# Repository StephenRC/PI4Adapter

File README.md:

# PI4Adapter
PI3 or PI4 to Duet 3

Duet 3 Mini 5+ mount directly on it with the board hanging off the side,  5vdc required.

Deut 3 6HC, mount of the board, needs a extension to the 26 pin socket to get the board high enough.  PI4 requires external 5vdc.

The JST-XH is for addons, like the official PI Touchscreen

Round Trakcs plugin used.  Add it in with the KiCAD plugin mamnager.

USB C connector: Didn't fit, adjusted it.  Need to test again

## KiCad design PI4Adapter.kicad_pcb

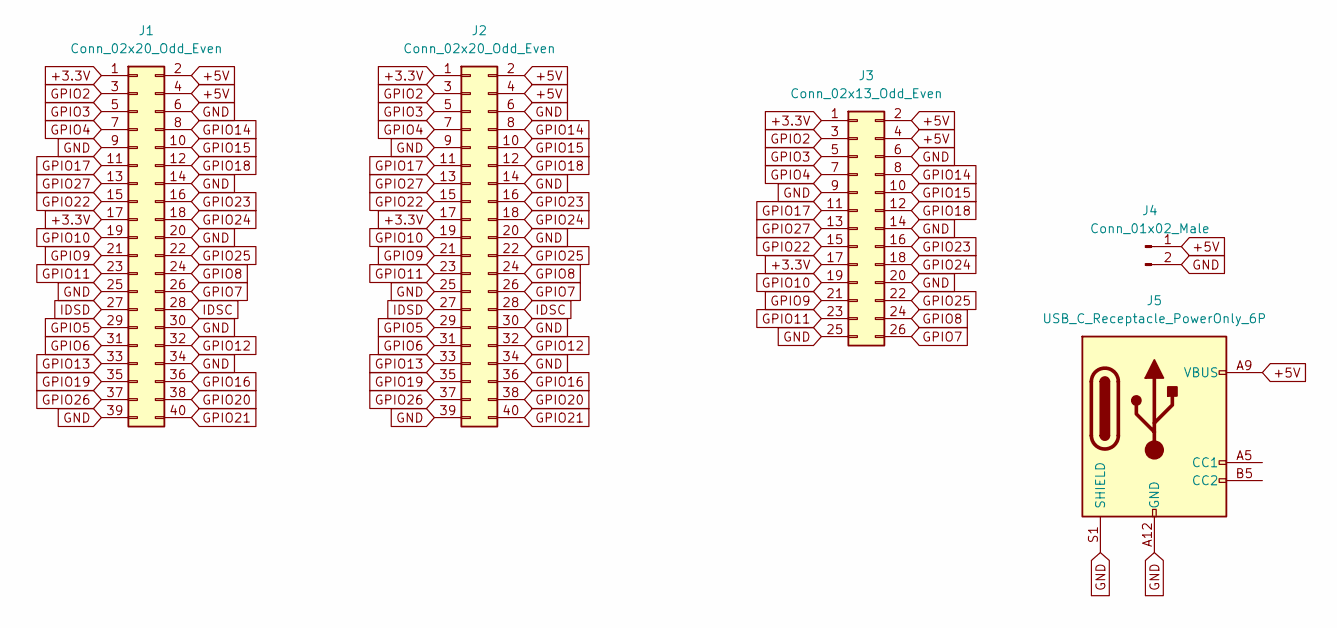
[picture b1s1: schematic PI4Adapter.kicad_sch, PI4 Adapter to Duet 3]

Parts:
J1: Conn_02x20_Odd_Even; PinSocket_2x20_P2.54mm_Vertical
J2: Conn_02x20_Odd_Even; PinHeader_2x20_P2.54mm_Vertical
J3: Conn_02x13_Odd_Even; PinSocket_2x13_P2.54mm_Vertical
J4: Conn_01x02_Male; JST_XH_S2B-XH-A_1x02_P2.50mm_Horizontal
J5: USB_C_Receptacle_PowerOnly_6P; USB_C_Receptacle_GCT_USB4135-GF-A_6P_TopMnt_Horizontal

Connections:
+3.3V: J1.1, J1.17, J2.1, J2.17, J3.1, J3.17
+5V: J1.2, J1.4, J2.2, J2.4, J3.2, J3.4, J4.1, J5.A9 (VBUS), J5.B9 (VBUS)
GND: J1.6, J1.9, J1.14, J1.20, J1.25, J1.30, J1.34, J1.39, J2.6, J2.9, J2.14, J2.20, J2.25, J2.30, J2.34, J2.39, J3.6, J3.9, J3.14, J3.20, J3.25, J4.2, J5.A12 (GND), J5.B12 (GND), J5.S1 (SHIELD)
GPIO2: J1.3, J2.3, J3.3
GPIO3: J1.5, J2.5, J3.5
GPIO4: J1.7, J2.7, J3.7
GPIO5: J1.29, J2.29
GPIO6: J1.31, J2.31
GPIO7: J1.26, J2.26, J3.26
GPIO8: J1.24, J2.24, J3.24
GPIO9: J1.21, J2.21, J3.21
GPIO10: J1.19, J2.19, J3.19
GPIO11: J1.23, J2.23, J3.23
GPIO12: J1.32, J2.32
GPIO13: J1.33, J2.33
GPIO14: J1.8, J2.8, J3.8
GPIO15: J1.10, J2.10, J3.10
GPIO16: J1.36, J2.36
GPIO17: J1.11, J2.11, J3.11
GPIO18: J1.12, J2.12, J3.12
GPIO19: J1.35, J2.35
GPIO20: J1.38, J2.38
GPIO21: J1.40, J2.40
GPIO22: J1.15, J2.15, J3.15
GPIO23: J1.16, J2.16, J3.16
GPIO24: J1.18, J2.18, J3.18
GPIO25: J1.22, J2.22, J3.22
GPIO26: J1.37, J2.37
GPIO27: J1.13, J2.13, J3.13
IDSC: J1.28, J2.28
IDSD: J1.27, J2.27

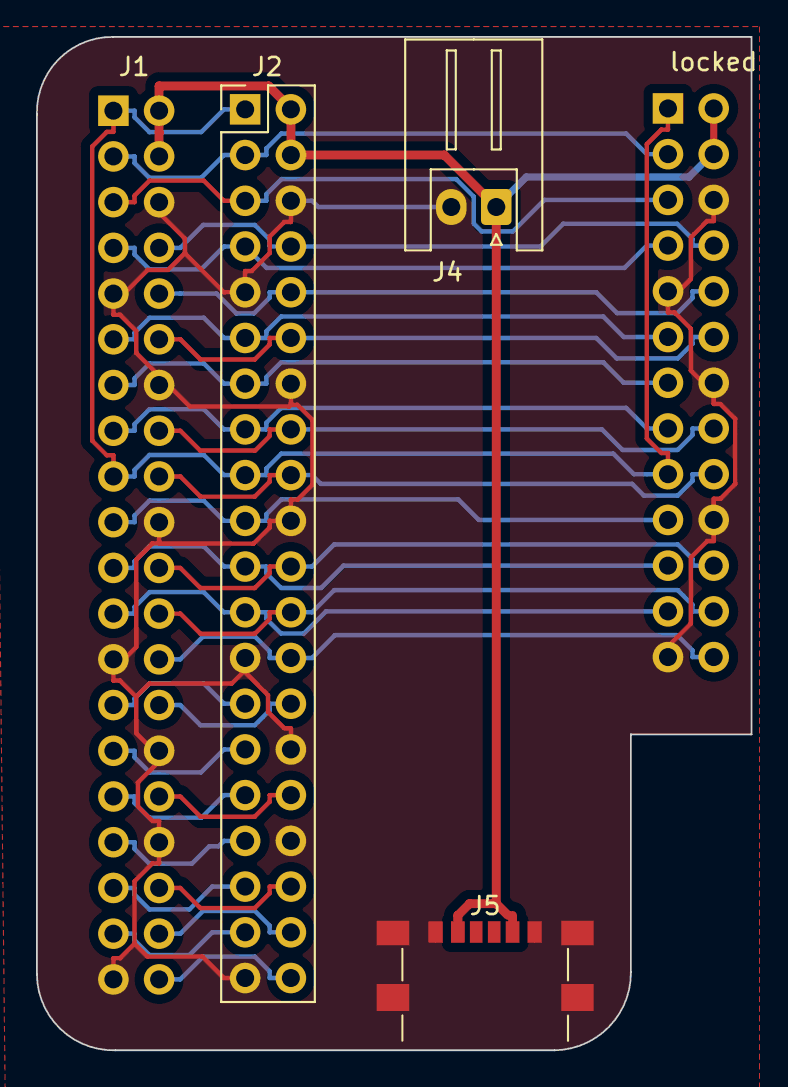
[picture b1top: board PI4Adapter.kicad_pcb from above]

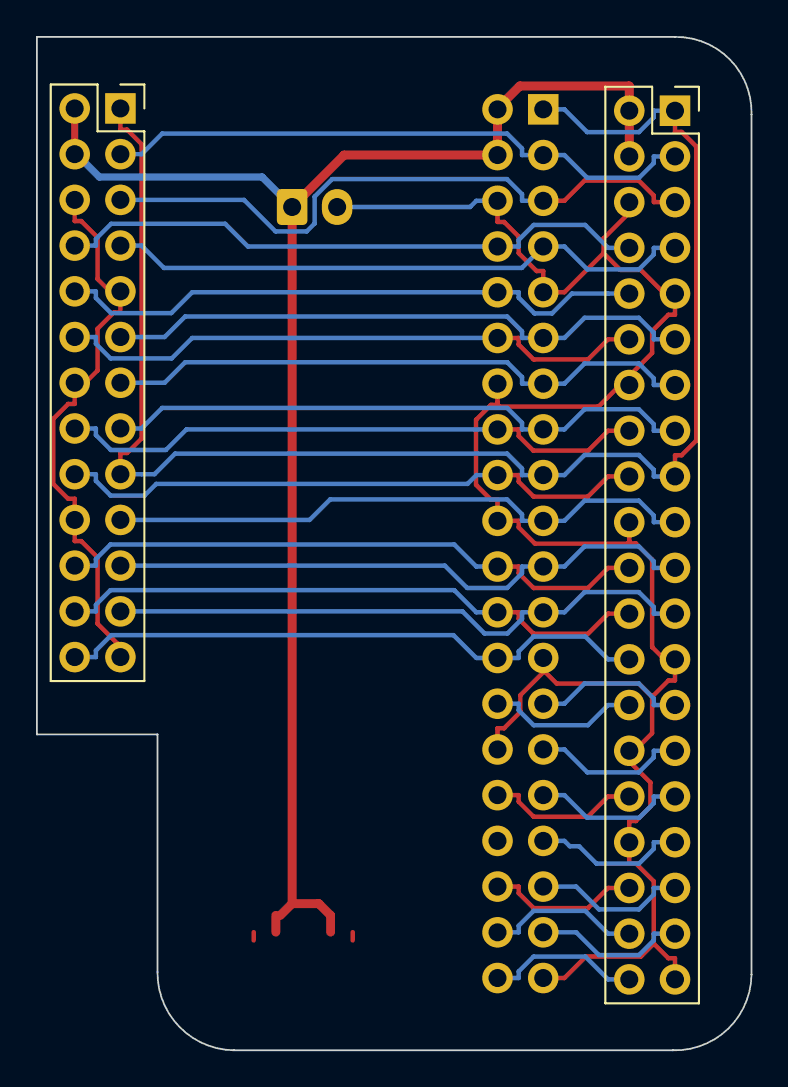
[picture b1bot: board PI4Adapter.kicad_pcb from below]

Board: 2 copper layers, 39.7 x 56.3 mm, 5 parts (2 on the bottom side), 31 nets.

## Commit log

2022-02-26 Initial Upload
    Connects a PI3 or PI4 to a Duet 3.
2022-02-26 Update README.md
    Added descriptions
2022-02-27 Update (Photos)
2022-04-09 Update
    backup files that kicad makes

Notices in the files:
PI4Adapter.kicad_pcb:
creativecommons.org/licenses/by-sa/4.0
PI4Adapter.kicad_sch:
creativecommons.org/licenses/by-sa/3.0
